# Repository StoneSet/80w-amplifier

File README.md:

# PROJECT 3A - ESP
## The Eagle project of the P3A project of Elliott Rod (ESP)

**(c) Found the entire project here: http://sound.whsites.net/project3a.htm**

## Included:
1. All needed files to modify the project
2. BOM

## Some img's :

------

# 

(c) Elliott Rod & StoneSet - http://sound.whsites.net - http://stoneset.github.io/ (2019)

plz do not steal, i'm not the owner of this project, i'm only the owner of this pcb. Have fun !

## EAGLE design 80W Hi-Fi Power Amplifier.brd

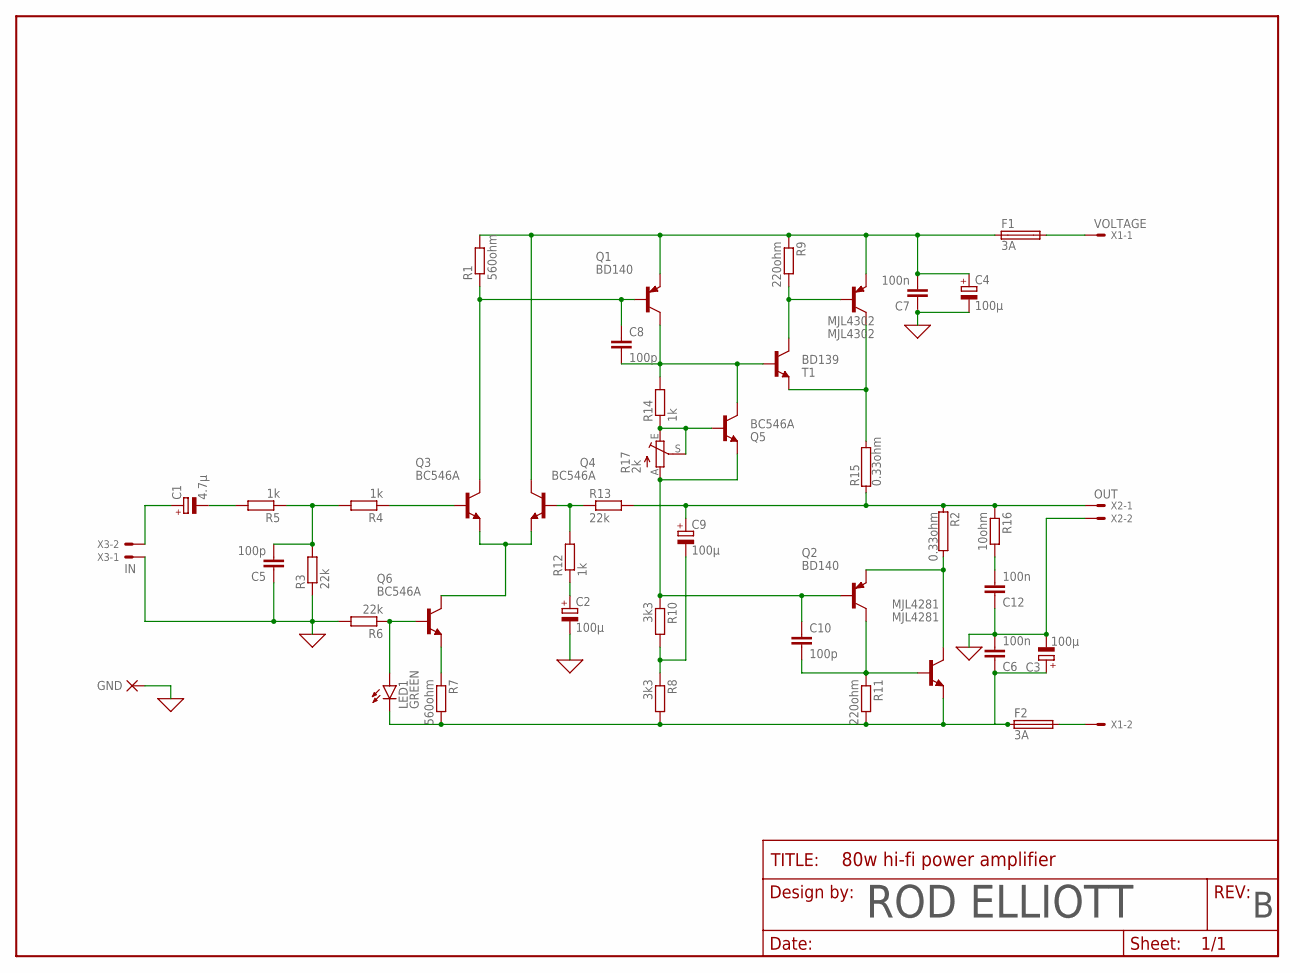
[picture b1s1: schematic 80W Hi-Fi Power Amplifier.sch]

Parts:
C1: 4.7µ; E2-5
C2, C3, C4: 100µ; E3,5-8
C5, C8, C10: 100p; C025-024X044
C6, C7, C12: 100n; C025-024X044
C9: 100µ; E3,5-10
F1, F2: 3A; FUSE_HOLDER_5X20MM
FRAME1: FRAME-LETTERNO_PACKAGE; DUMMY
GND: PAD-SMD20S; SMD20S
LED1: GREEN; LED5MM
MJL4281: MJL4281; TO-264
MJL4302: MJL4302; TO-264
Q1, Q2: BD140; TO126
Q3, Q4, Q5, Q6: BC546A; TO92-EBC
R1, R7: 560ohm; 0207/10
R2, R15: 0.33ohm; HPS923
R3, R6, R13: 22k; 0207/10
R4, R5, R12, R14: 1k; 0207/10
R8, R10: 3k3; 0309/10
R9, R11: 220ohm; 0207/10
R16: 10ohm; 0309/10
R17: 2k; CA6V
T1: BD139; TO126
X1: VOLTAGE; 22-23-2021
X2: OUT; 22-23-2021
X3: IN; 22-23-2021

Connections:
0: C2.-, C3.-, C4.-, C5.1, C6.2, C7.1, C12.1, GND.PAD, R3.1, R6.2, X2.2, X3.1
unnamed: C5.2, R3.2, R4.2, R5.1
unnamed: C1.-, R5.2
unnamed: C12.2, R16.2
unnamed: C9.-, R8.1, R10.2
unnamed: Q3.B, R4.1
unnamed: Q6.E, R7.1
unnamed: LED1.A, Q6.B, R6.1
unnamed: C2.+, R12.1
unnamed: Q4.B, R12.2, R13.1
unnamed: Q3.E, Q4.E, Q6.C
unnamed: Q5.B, R14.1, R17.E, R17.S
unnamed: C8.2, Q1.2 (C), Q5.C, R14.2, T1.3 (B)
unnamed: MJL4302.C, R15.2, T1.1 (E)
unnamed: C8.1, Q1.3 (B), Q3.C, R1.1
unnamed: MJL4302.B, R9.2, T1.2 (C)
unnamed: MJL4281.C, Q2.1 (E), R2.2
unnamed: C4.+, C7.2, F1.1, MJL4302.E, Q1.1 (E), Q4.C, R1.2, R9.1
unnamed: C3.+, C6.1, F2.1, LED1.K (C), MJL4281.E, R7.2, R8.2, R11.2
unnamed: C1.+, X3.2
unnamed: C9.+, R2.1, R13.2, R15.1, R16.1, X2.1
unnamed: C10.2, MJL4281.B, Q2.2 (C), R11.1
unnamed: C10.1, Q2.3 (B), Q5.E, R10.1, R17.A
unnamed: F2.2, X1.2
unnamed: F1.2, X1.1

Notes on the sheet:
ROD ELLIOTT

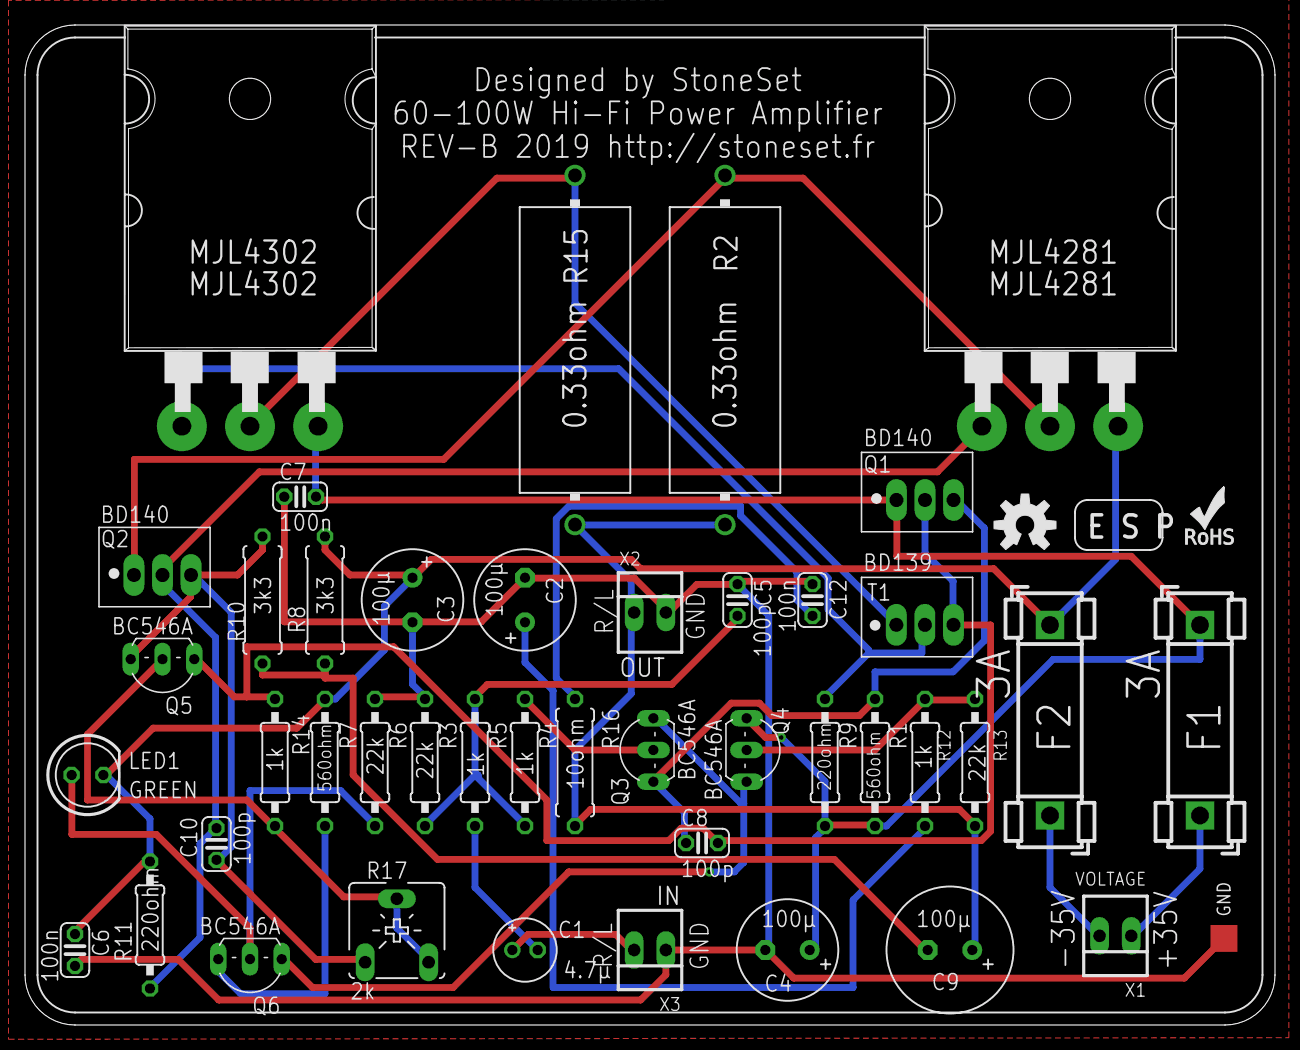
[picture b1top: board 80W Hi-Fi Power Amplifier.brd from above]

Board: 2 copper layers, 100.0 x 80.0 mm, 47 parts (0 on the bottom side), 25 nets.

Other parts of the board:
U$1: OSHW-LOGO-M
U$2: ROHS_LOGO_0.18_IN

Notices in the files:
parts and their libraries:
SparkFun-Aesthetics: Licensing: Creative Commons ShareAlike 4.0 International - https://creativecommons.org/licenses/by-sa/4.0
dpads: Copyright (C) 2004, Bob Starr (bobstarr@mindspring.com)
SparkFun-Aesthetics: Released under the Creative Commons Attribution Share-Alike 4.0 License
